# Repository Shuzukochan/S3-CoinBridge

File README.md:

# S3-CoinBridge

**Carrier PCB (Shield) cho ESP32-S3 DevKit kết nối bộ nhận tiền xu JY-133A và nguồn tổ ong 12V cho Photobooth.**

---

## 📌 Tổng quan dự án

`S3-CoinBridge` là bo mạch trung gian phần cứng (Carrier Board) chuẩn công nghiệp, thiết kế để cắm trực tiếp module **ESP32-S3-DevKitC-1** (2x22 pin), nhận nguồn ngoài 12V từ nguồn tổ ong và giao tiếp an toàn với bộ nhận xu **JY-133A**.

* **Kích thước bo mạch:** 70.0 mm x 62.0 mm (siêu gọn, tối ưu không gian tủ máy Photobooth).
* **Số lớp:** 2 lớp (Top Copper + Bottom Copper Solid Ground Plane).
* **Mass chung (Common GND):** Mặt đáy phủ đồng mass GND liền khối, chống nhiễu vượt trội.
* **Tầng chuyển mức & bảo vệ:** Sử dụng Optocoupler **PC817** cách ly điện áp 12V $\rightarrow$ 3.3V, triệt tiêu 100% xung cảm ứng ngược (inductive kickback) từ cuộn hút solenoid của JY-133A, bảo vệ tuyệt đối ESP32 và Mac mini kết nối qua USB Serial.

---

## 🖼️ Hình ảnh 3D Render

| Góc nhìn từ trên (Top View) | Phối cảnh 3D (Isometric View) |
| :---: | :---: |
|  |  |

---

## 🔌 Sơ đồ kết nối & Chân cắm (Pinout)

### 1. Nguồn vào 12V (J1: KF301-2P / MKDS 5.08mm)
*Mặt cắm dây hướng ra cạnh ngoài bên trái bo mạch.*
* **Chân 1 `(+)`:** Nối vào ngõ `+12V` của nguồn tổ ong. (Có diode Schottky **SS34** 3A chống cắm ngược cực).
* **Chân 2 `(-)`:** Nối vào ngõ `COM / GND` của nguồn tổ ong.

### 2. Cổng kết nối JY-133A (J2: XH2.54 4-Pin)
*Thứ tự chân chuẩn của giắc cắm JY-133A đi kèm nhà sản xuất:*
* **Chân 1 (Đỏ):** `+12V` (Cấp nguồn nuôi cho đầu đọc xu).
* **Chân 2 (Trắng):** `COIN Signal` (Tín hiệu xung Open-Collector kích hoạt mức thấp khi có xu hợp lệ).
* **Chân 3 (Đen):** `GND` (Mass nguồn).
* **Chân 4 (Xám):** `NC` (Không kết nối / Counter line).

### 3. Đèn LED chỉ thị trạng thái
* **LED1 (Đỏ - PWR):** Sáng liên tục khi có nguồn 12V cấp vào bo.
* **LED2 (Xanh lá - COIN):** Nhấp nháy đồng bộ theo từng xung khi khách bỏ xu vào JY-133A.

### 4. Giao tiếp với ESP32-S3 DevKit
* **Chân GPIO5 (J3 Pin 5):** Nhận xung logic 3.3V (Mặc định mức HIGH nhờ trở kéo 10k R3; khi có xung xu, PC817 dẫn kéo GPIO5 xuống mức LOW). Khớp hoàn toàn với firmware config `COIN_GPIO = 5`.
* **Tụ lọc C3 (100nF):** Lọc rung phần cứng (hardware debouncing) giúp ESP32 đếm xung chính xác 100%, không bị xung ảo do nhiễu EMI.
* **Cổng USB-C (TOP):** Hướng lên cạnh trên bo mạch, cắm cáp USB về Mac mini chạy app Photobooth.

---

## 📋 Danh mục linh kiện (Bill of Materials - BOM)

| STT | Ký hiệu | Giá trị / Mã linh kiện | Footprint | Ghi chú |
| :---: | :--- | :--- | :--- | :--- |
| 1 | **U1** | PC817 (Sharp / Everlight) | DIP-4_W7.62mm | Optocoupler |
| 2 | **D1** | SS34 (3A / 40V Schottky) | SMA (DO-214AC) | Diode chống ngược cực |
| 3 | **C1** | 220µF / 25V | CP_Radial_D8.0mm_P3.50mm | Tụ hóa lọc nguồn 12V |
| 4 | **C2, C3** | 100nF (0.1µF) / 50V | C_0805_2012Metric | Tụ gốm lọc nhiễu SMD |
| 5 | **R1** | 2.2kΩ (1/8W, 5%) | R_0805_2012Metric | Trở hạn dòng LED PWR |
| 6 | **R2** | 1.0kΩ (1/4W, 5%) | R_0805_2012Metric | Trở hạn dòng LED COIN & Opto |
| 7 | **R3** | 10kΩ (1/8W, 5%) | R_0805_2012Metric | Trở kéo 3.3V GPIO5 |
| 8 | **LED1** | LED Đỏ (Red) | LED_0805_2012Metric | Báo nguồn |
| 9 | **LED2** | LED Xanh lá (Green) | LED_0805_2012Metric | Báo xung xu |
| 10 | **J1** | KF301-2P (Pitch 5.08mm) | MKDS-1,5-2-5.08 | Terminal vặn ốc nguồn 12V |
| 11 | **J2** | JST XH 4-Pin (Pitch 2.50/2.54mm) | JST_XH_B4B-XH-A_Vertical | Cắm dây JY-133A |
| 12 | **J3, J4** | Header rào cái 1x22 Pin (Pitch 2.54mm) | PinSocket_1x22_Vertical | Cắm ESP32-S3 DevKit |
| 13 | **H1 - H4** | Lỗ bắt ốc M3 | MountingHole_3.2mm_M3 | Bắt cố định vào tủ máy |

---

## 🚀 Hướng dẫn mở dự án trên KiCad

Dự án được tạo trên **KiCad 10.0** và đã được đóng gói **đầy đủ thư viện độc lập (Portable)**:
* **Thư viện Footprint nội bộ:** `S3-CoinBridge.pretty/` (Kèm bảng ánh xạ `fp-lib-table`).
* **Thư viện Symbol nội bộ:** `S3-CoinBridge.kicad_sym` (Kèm bảng ánh xạ `sym-lib-table`).

👉 **Bất kỳ máy tính nào cài KiCad (Windows, macOS, Linux) chỉ cần tải thư mục này về và mở file `S3-CoinBridge.kicad_pro` là xem, chỉnh sửa, xuất file bình thường mà không bị thiếu linh kiện.**

---

## 🏭 Đặt gia công sản xuất mạch (JLCPCB / PCBWay)

Toàn bộ file sản xuất đã được nén sẵn trong:
📦 **[`S3-CoinBridge-Gerbers.zip`](S3-CoinBridge-Gerbers.zip)**

**Thông số khuyên dùng khi đặt mạch:**
* **Dimensions:** 70 mm x 62 mm
* **Layer Count:** 2 Layers
* **PCB Thickness:** 1.6 mm
* **Copper Weight:** 1 oz
* **Surface Finish:** HASL with lead (hoặc LeadFree HASL / ENIG)
* **Solder Mask Color:** Xanh lá / Đen / Xanh dương

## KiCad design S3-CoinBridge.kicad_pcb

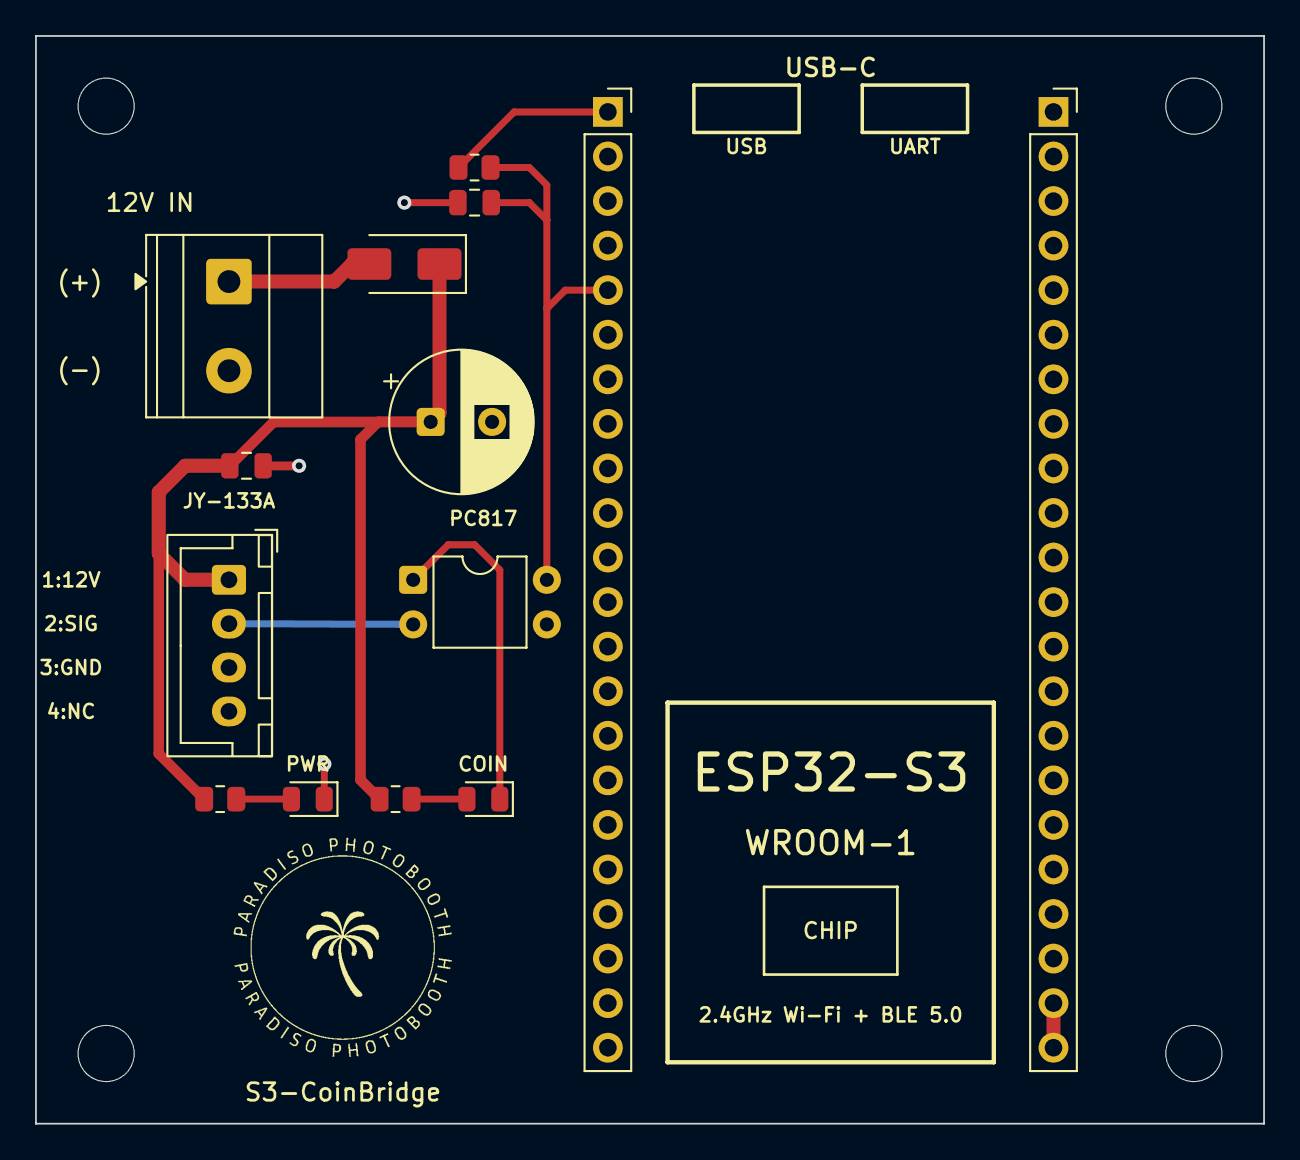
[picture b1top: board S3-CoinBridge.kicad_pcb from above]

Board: 2 copper layers, 70.0 x 62.0 mm, 19 parts (0 on the bottom side), 9 nets.

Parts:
C1: 220uF; CP_Radial_D8.0mm_P3.50mm
C2, C3: 100nF; C_0805_2012Metric
D1: SS34; D_SMA
H1, H2, H3, H4: M3; MountingHole_3.2mm_M3
J1: 12V IN; TerminalBlock_Phoenix_MKDS-1,5-2-5.08_1x02_P5.08mm_Horizont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
J2: JY-133A; JST_XH_B4B-XH-A_1x04_P2.50mm_Vertical
J3: ESP32-S3 Left; PinSocket_1x22_P2.54mm_Vertical
J4: ESP32-S3 Right; PinSocket_1x22_P2.54mm_Vertical
LED1: PWR Red; LED_0805_2012Metric
LED2: COIN Grn; LED_0805_2012Metric
LOGO1: LOGO_PARADISO
R1: 2.2k; R_0805_2012Metric
R2: 1k; R_0805_2012Metric
R3: 10k; R_0805_2012Metric
U1: PC817; DIP-4_W7.62mm

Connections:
+12V: C1.1, C2.1, D1.1, J2.1, R1.1, R2.1
COIN_SIGNAL: J2.2, U1.2
ESP32_3V3: J3.1, R3.1
ESP32_GPIO5: C3.1, J3.5, R3.2, U1.4
GND: C1.2, C2.2, C3.2, J1.2, J2.3, J4.1, J4.21, J4.22, LED1.1, U1.3
unnamed: D1.2, J1.1
unnamed: LED1.2, R1.2
unnamed: LED2.2, R2.2
unnamed: LED2.1, U1.1

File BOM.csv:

STT,Mã linh kiện (Ref),Tên linh kiện & Thông số,Quy cách đóng gói (Package),SL / 1 Bo,SL cho 5 Bo,SL nên đặt mua (Dự phòng),Mã / Từ khóa Thế Giới IC,Đơn giá ước tính (VND),Thành tiền ước tính (VND),Link mua Thế Giới IC,Ghi chú ứng dụng
1,D1,Diode Schottky SS34 (3A / 40V),SMA (DO-214AC),1,5,8,SS34 (DO-214AC),"1,200","9,600",https://www.thegioiic.com/tim-kiem?q=SS34+SMA,Chống cắm ngược cực nguồn 12V IN
2,C1,Tụ hóa nhôm 220uF 25V (hoặc 35V),"Radial D8mm, P3.5mm (THT)",1,5,6,220uF 25V (8x12mm),"1,000","6,000",https://www.thegioiic.com/tim-kiem?q=tu+hoa+220uF+25V,"Lọc nguồn 12V chính, đường kính D=8mm"
3,"C2, C3",Tụ gốm 100nF (0.1uF / 104) 50V,SMD 0805,2,10,20,IC262,250,"5,000",https://www.thegioiic.com/tu-gom-smd-0805-100nf-50v-10-samsung,"C2 lọc nguồn 12V, C3 lọc rung debounce chân GPIO5"
4,U1,Optocoupler PC817 (PC817C / EL817),DIP-4 (THT),1,5,6,IC18785,"3,100","18,600",https://www.thegioiic.com/tim-kiem?q=PC817+DIP-4,Cách ly quang bảo vệ ESP32 khỏi xung 12V
5,R1,Điện trở 2.2k Ohm (2K2) 5%,SMD 0805,1,5,15,Điện trở 0805 2.2k,150,"2,250",https://www.thegioiic.com/tim-kiem?q=dien+tro+0805+2.2k,Hạn dòng cho LED PWR Đỏ từ nguồn 12V
6,R2,Điện trở 1k Ohm (1K) 5%,SMD 0805,1,5,15,Điện trở 0805 1k,150,"2,250",https://www.thegioiic.com/tim-kiem?q=dien+tro+0805+1k,Hạn dòng cho LED phát PC817 & LED COIN Xanh
7,R3,Điện trở 10k Ohm (10K) 5%,SMD 0805,1,5,15,Điện trở 0805 10k,150,"2,250",https://www.thegioiic.com/tim-kiem?q=dien+tro+0805+10k,Điện trở kéo lên (Pull-up) 3.3V cho chân GPIO5
8,LED1,LED Đỏ (Red) SMD,SMD 0805,1,5,10,20000,500,"5,000",https://www.thegioiic.com/tim-kiem?q=LED+0805+do,Báo nguồn 12V chính (PWR)
9,LED2,LED Xanh Lá (Green) SMD,SMD 0805,1,5,10,IC19471 / 20007,500,"5,000",https://www.thegioiic.com/tim-kiem?q=LED+0805+xanh+la,Báo xung khi khách nhét xu (COIN)
10,J1,Terminal Block 2P 5.08mm (KF301-2P),Pitch 5.08mm (THT),1,5,6,IC7864,"2,000","12,000",https://www.thegioiic.com/dau-noi-day-kf301-2-v-5-08mm-xuyen-lo,Cổng cấp nguồn 12V DC dạng ốc siết
11,J2,Đầu Header XH2.54 4P thẳng (Đực),"XH-4A, Pitch 2.54mm (THT)",1,5,6,IC2012,"1,000","6,000",https://www.thegioiic.com/dau-xh2-54mm-4-chan-thang-xuyen-lo,Cắm cáp kết nối trực tiếp bộ nhận xu JY-133A
12,"J3, J4",Hàng rào cái 1x40P 2.54mm (Chân thẳng),Pitch 2.54mm (THT),2,10,11,Hàng rào cái 1x40 2.54mm,"2,500","27,500",https://www.thegioiic.com/tim-kiem?q=hang+rao+cai+1x40+2.54mm,Mỗi bo cần 2 hàng 22P. Mua thanh 40P cắt/bẻ thành 22P
13,Phụ kiện,Trụ đồng M3x10mm (Đực-Cái) + Ốc M3,M3 (Lỗ bo 3.2mm),4,20,20,Trụ đồng M3x10,"1,500","30,000",https://www.thegioiic.com/tim-kiem?q=tru+dong+M3x10,4 chân đế bắt ốc cố định bo mạch vào vỏ tủ photobooth
